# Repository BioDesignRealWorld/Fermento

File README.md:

Fermento
========

An open-source incubator for fun and profit. For more information about the project, see [biodesign.cc](http://biodesign.cc/2013/12/25/diy-incubator/).

Board
-----

* __Fab__ contains the PCB version to send to a professional PCB fabrication house. It has a nice silkscreen and slightly better component layout. 
* __Homebrew__ contains the version for homebrew PCB printing. The layout is one-sided for easier manufacturing. Drill plan and assembly instruction sheet included.
  To accomodate a single sided board, the wiring of the component to the microcontroller had to be changed. The correct pin mapping can be changed by a single line
  in the firmware.

Bill Of Material
----------------

* 1x ATmega328p
* 1x DIP28 socket 
* 2x Tactile switch (through hole) (BUTTON1, BUTTON2) (C&K PTS645SM95-2 LFS)
* 2x Resistor 10K (R1, R3)
* 1x Resistor 1K (R2)
* 4x Capacitor 0.1uF, 2.5 mm pin spacing (C1, C2, C3, C5)
* 1x Electrolytic capacitor 47uF, radial, 2.5 mm pin spacing (C4)
* 1x 6-pin 90-degrees header (SERIAL)
* 1x 3x2-pin straight header (ISP)
* 1x 6-terminal screw block (Altech MBE-156)
* 1x Relay, 3VDC switching (Omron G6RL-1A-DC3)
* 1x 13mm buzzer (BUZZ1) (Murata, PKM13EPYH4000-A0)
* 1x DC jack 2.1mm (Kobiconn 163-179PH-EX)
* 1x 32.768kHz crystal (Q1) (ECS-.327-12.5-13X)
* 1x Mosfet transistor, TO92 (Q2) (Supertex TP2104N3-G)
* 1x 3.3V Regulator, TO220 (REG1) (TI TLV2217-33KCSE3)
* 1x Temperature sensor, TO92 (TEMP1) (TI LM61CIZ/NOPB)
* 1x 7-segment 4-digit display (7SEG) (Lumex LDQ-N514RI)

Wiring of the incubator
-----------------------

The board has a 6 pin terminal that allows minimal effort in wiring all the AC part of the circuit.

* The 2 wires from the bulb socket go into __LOAD__.
* The 2 wires from the plug go into one of the __AC IN__ terminal.
* The second __AC IN__ can be used to attach a female AC socket. This allows to connect there a DC outlet to power the board.

Power supply
------------

The board has a 2.1mm DC jack. The DC regulator requires an input of 3-12V DC.

Firmware
--------

To install the firmware in your Arduino IDE, do the following.

* Copy the folder `firmware/Fermento` to your local Arduino folder.
* Copy the content of `firmware/hardware` to local `Arduino/hardware`.
* Copy the content of `firmware/libraries` to local `Arduino/libraries`.

Then, chose `Tools -> Board -> ATmega328p on a breadboard`. Choose the sketch
`Fermento` from the sketchbook, and upload it.

In case you don't use the homebrew version, there is one line to comment out in
the sketch to change the pin mapping.

In the Fab version, an ISP header is provided to burn the bootloader. The Homebrew
version is lacking this, so a different board (such as the standard Arduino) needs
to be used to burn the bootloader. In addition, an ISP-programmer is needed.
An Arduino board can also be used to do [the job](http://arduino.cc/en/Tutorial/ArduinoISP).

Use it
------

Button1 and button2 control the incubation temperature and time respectively.

When button1 is shortly pressed the display switches to temperature. To set the
incubation temperature, keep button1 pressed until it displays the desired
temperature. The temperature regulation starts as soon as an incubation
temperatures different than 0 is set. Note that if the incubation temperature
is lower than room temperature, nothing happens.

When button2 is shortly pressed the display switches to incubation time
(hours:minutes). To set the incubation time, keep button2 pressed until the
desired incubation time is displayed. If you don’t set an incubation time, the
incubation will never stop. The time goes up in increments of 30 minutes.

Pressing button1 and button2 together for a few seconds resets incubation temperature and time to 0.

License
-------

2013 (c) Robin Scheibler, [CC BY-SA 3.0](https://creativecommons.org/licenses/by-sa/3.0/).

Based on [TokyoTime](http://robinscheibler.org/TokyoTime), itself based on SparkFun's [BigTime](https://www.sparkfun.com/products/11734).

The code uses the [Arduino PID library](http://playground.arduino.cc/Code/PIDLibrary).

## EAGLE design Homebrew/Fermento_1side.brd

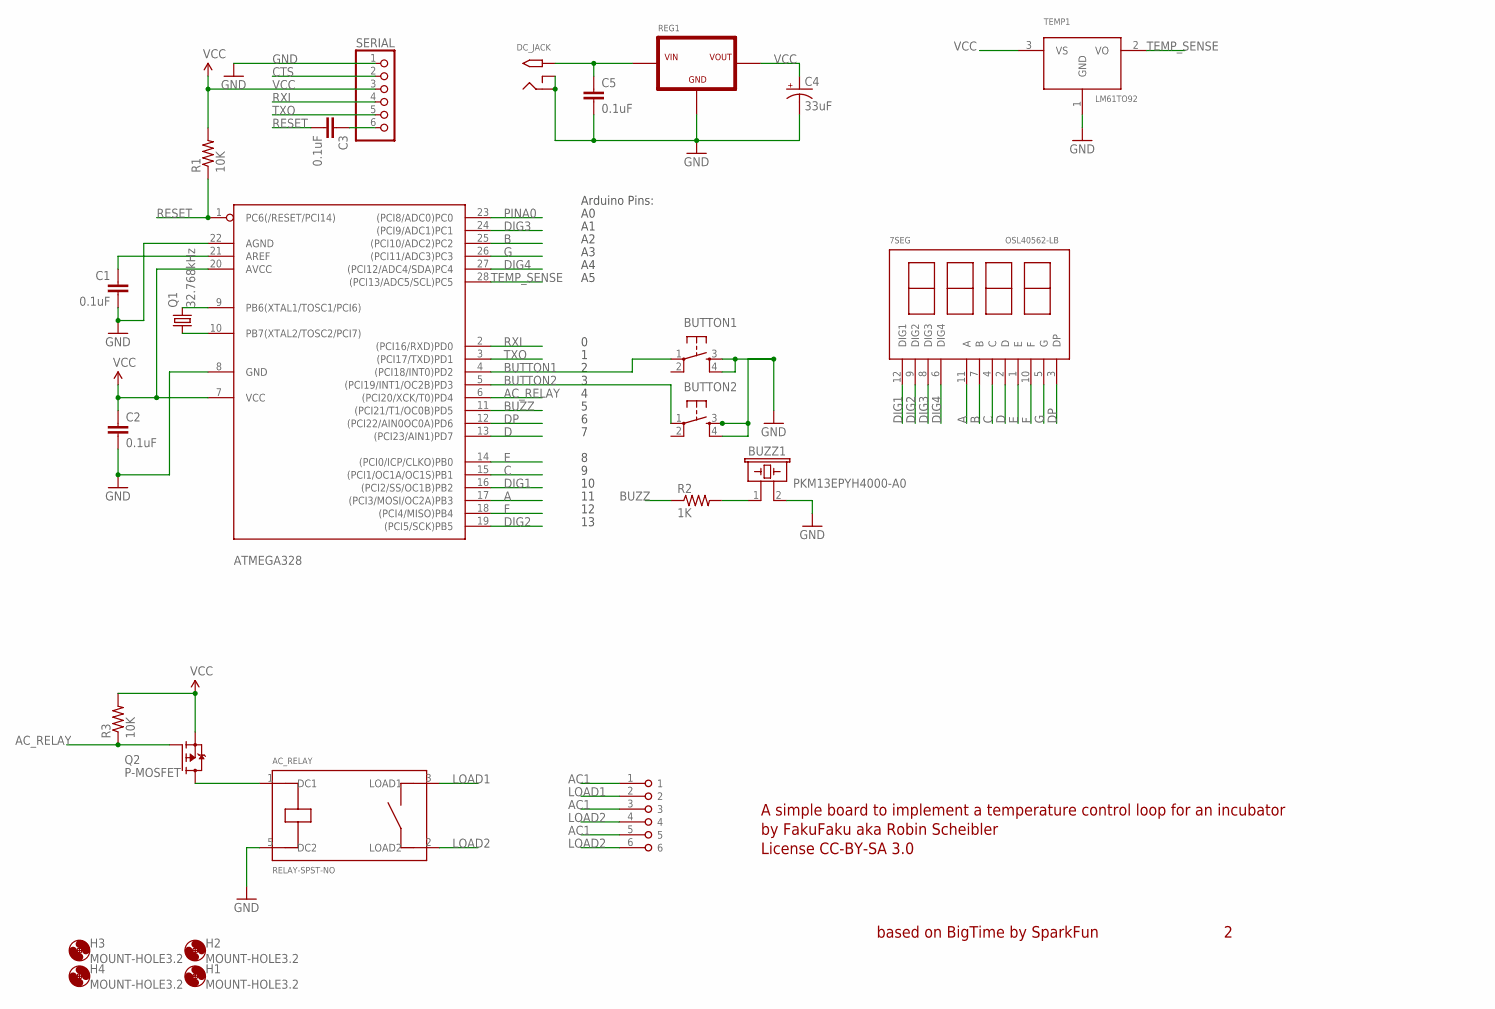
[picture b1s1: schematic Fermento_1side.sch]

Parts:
7SEG: OSL40562-LB; OSL40562
AC_RELAY: RELAY-SPST-NO; G6RL-1A-DC3
ATMEGA328: ATMEGA168-20P; DIL28-3
BUTTON1, BUTTON2: TAC_SWITCHPTH; TACTILE-PTH
BUZZ1: PKM13EPYH4000-A0; PIEZO-MURATA-13MM
C1, C2, C3, C5: 0.1uF; CAP-PTH-SMALL
C4: 33uF; CPOL-RADIAL-10UF-25V
DC_JACK: 2.1MMJACKTHM; PJ-102A
H1, H2, H3, H4: MOUNT-HOLE3.2; 3,2
Q1: 32.768kHz; CRYSTAL-8X3-TH
Q2: P-MOSFET; TO92-
R1, R3: 10K; 0207/10
R2: 1K; 0207/10
REG1: REGULATOR-NOTHERMAL-TO220-STRAIGHT; TO-220-STRAIGHT
SERIAL: PINHD-1X6/90; 1X06/90
TEMP1: LM61TO92; TO92-
U$2: TERMINAL-6; MBE-156

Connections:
A: 7SEG.11 (A), ATMEGA328.17 ((PCI3/MOSI/OC2A)PB3)
AC1: U$2.1, U$2.3, U$2.5
AC_RELAY: ATMEGA328.6 ((PCI20/XCK/T0)PD4), Q2.2 (G), R3.1
AREF: ATMEGA328.21 (AREF), C1.1
B: 7SEG.7 (B), ATMEGA328.25 ((PCI10/ADC2)PC2)
BUTTON1: ATMEGA328.4 ((PCI18/INT0)PD2), BUTTON1.1
BUTTON2: ATMEGA328.5 ((PCI19/INT1/OC2B)PD3), BUTTON2.1
BUZZ: ATMEGA328.11 ((PCI21/T1/OC0B)PD5), R2.1
C: 7SEG.4 (C), ATMEGA328.15 ((PCI1/OC1A/OC1S)PB1)
CTS: SERIAL.2
D: 7SEG.2 (D), ATMEGA328.13 ((PCI23/AIN1)PD7)
DIG1: 7SEG.12 (DIG1), ATMEGA328.16 ((PCI2/SS/OC1B)PB2)
DIG2: 7SEG.9 (DIG2), ATMEGA328.19 ((PCI5/SCK)PB5)
DIG3: 7SEG.8 (DIG3), ATMEGA328.24 ((PCI9/ADC1)PC1)
DIG4: 7SEG.6 (DIG4), ATMEGA328.27 ((PCI12/ADC4/SDA)PC4)
DP: 7SEG.3 (DP), ATMEGA328.12 ((PCI22/AIN0OC0A)PD6)
E: 7SEG.1 (E), ATMEGA328.14 ((PCI0/ICP/CLKO)PB0)
F: 7SEG.10 (F), ATMEGA328.18 ((PCI4/MISO)PB4)
G: 7SEG.5 (G), ATMEGA328.26 ((PCI11/ADC3)PC3)
GND: AC_RELAY.5 (DC2), ATMEGA328.8 (GND), ATMEGA328.22 (AGND), BUTTON1.3, BUTTON1.4, BUTTON2.3, BUTTON2.4, BUZZ1.2, C1.2, C2.2, C4.2 (-), C5.2, DC_JACK.RING, DC_JACK.RING_SW, REG1.CENTER (GND), SERIAL.1, TEMP1.1 (GND)
LOAD1: AC_RELAY.3 (LOAD1), U$2.2
LOAD2: AC_RELAY.2 (LOAD2), U$2.4, U$2.6
unnamed: ATMEGA328.9 (PB6(XTAL1/TOSC1/PCI6)), Q1.2
unnamed: ATMEGA328.10 (PB7(XTAL2/TOSC2/PCI7)), Q1.1
unnamed: C5.1, DC_JACK.TIP, REG1.LEFT (VIN)
unnamed: C3.1, SERIAL.6
unnamed: BUZZ1.1, R2.2
PINA0: ATMEGA328.23 ((PCI8/ADC0)PC0)
RELAY: AC_RELAY.1 (DC1), Q2.1 (D)
RESET: ATMEGA328.1 (PC6(/RESET/PCI14)), C3.2, R1.1
RXI: ATMEGA328.2 ((PCI16/RXD)PD0), SERIAL.4
TEMP_SENSE: ATMEGA328.28 ((PCI13/ADC5/SCL)PC5), TEMP1.2 (VO)
TXO: ATMEGA328.3 ((PCI17/TXD)PD1), SERIAL.5
VCC: ATMEGA328.7 (VCC), ATMEGA328.20 (AVCC), C2.1, C4.1 (+), Q2.3 (S), R1.2, R3.2, REG1.RIGHT (VOUT), SERIAL.3, TEMP1.3 (VS)

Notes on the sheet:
A simple board to implement a temperature control loop for an incubator
by FakuFaku aka Robin Scheibler
License CC-BY-SA 3.0
based on BigTime by SparkFun
Arduino Pins:

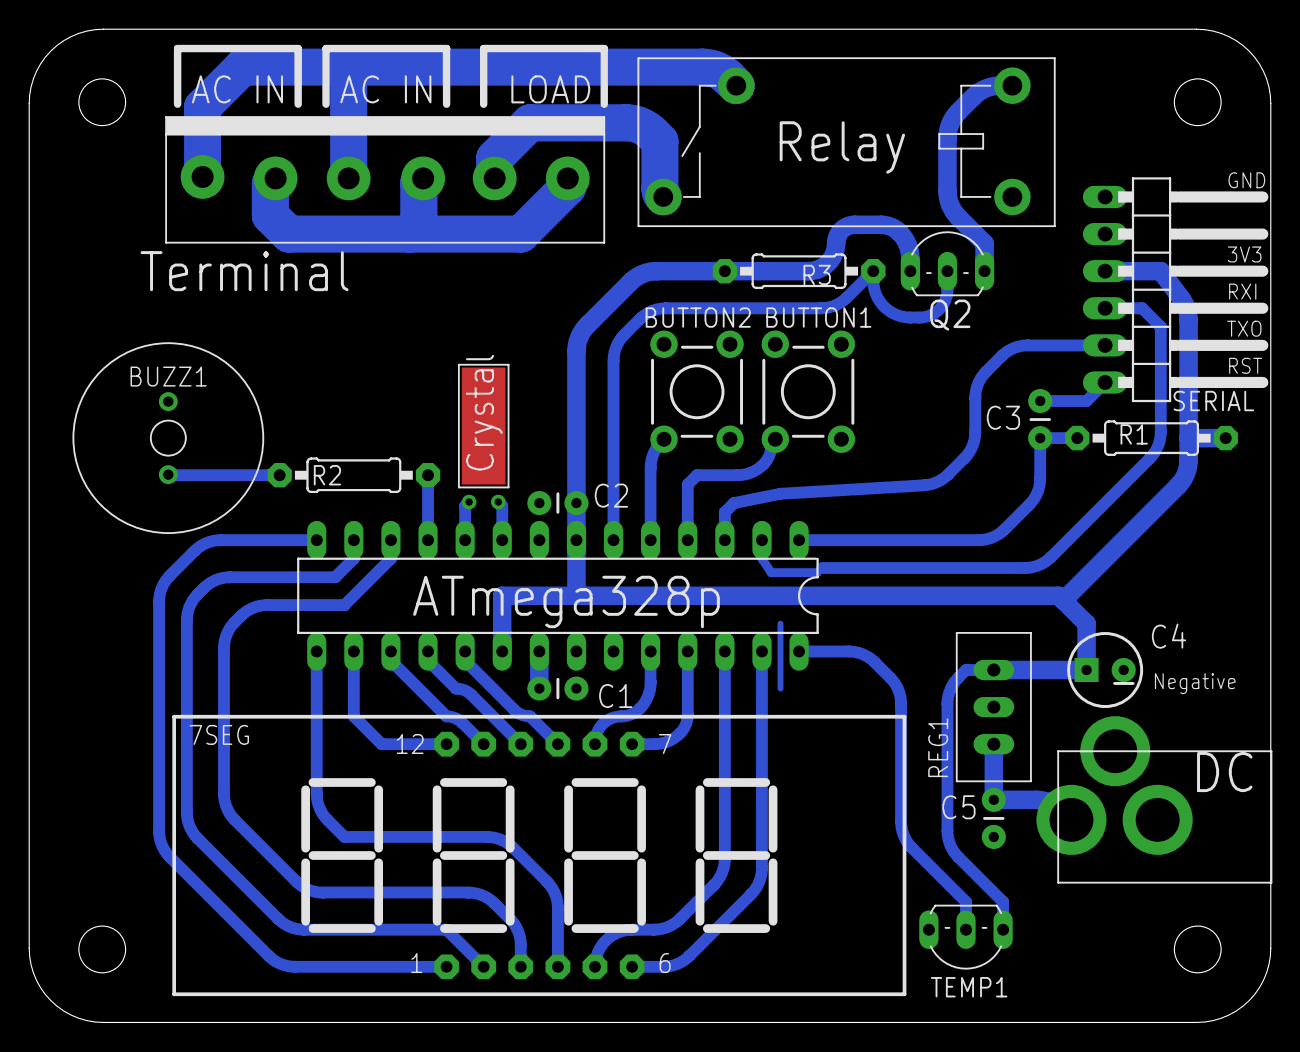
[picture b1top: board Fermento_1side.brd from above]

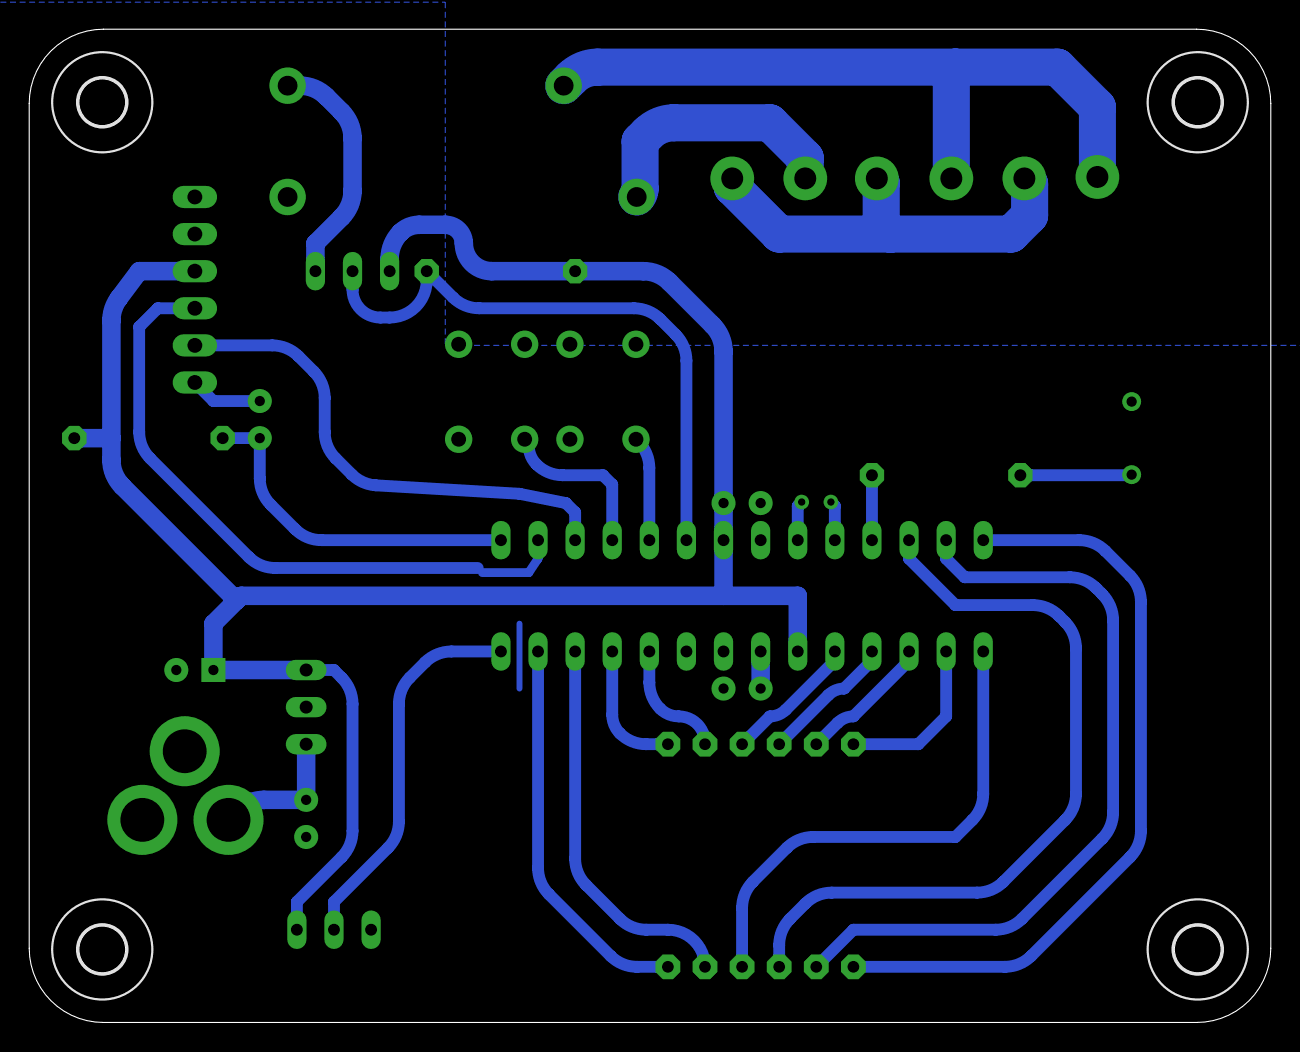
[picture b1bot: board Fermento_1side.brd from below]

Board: 2 copper layers, 85.0 x 68.0 mm, 25 parts (4 on the bottom side), 32 nets.

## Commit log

2013-11-19 Initial commit.
2013-11-19 Added the one-sided version.
2013-11-19 Added 1 sided version and png images.
2013-11-20 Added mask and info diagram for 1sided homebrew incubator.
2013-11-20 board difference added to README.
2013-11-20 One sided homebrew-friendly design redone.
2013-11-27 Added firmware to the repo.
2013-11-27 Added fermento arduino sketch.
2013-11-27 Updated license in Fermento sketch.
2013-11-28 README.
2013-11-29 BOM in README.
2013-12-04 Now incubator is on by default. Also there was a bug in reset function.
2013-12-25 Cleaned up for biodesign.cc post.
2013-12-25 Added license to readme.
2013-12-25 Bootloader footnote.
2014-01-10 Added the mask file for homebrew pcb.
2014-04-21 Fixed the time display bug. Fixed the seven sement digit_on/off segment_on/off bug.
2014-04-23 Fixed name of microcontroller in README and boards.txt file.
2014-04-23 Added kindof datasheet for Fab board.
2014-04-23 Added labels in the parts list.
2014-05-02 Remove a wrong pin pushed by mistake to the repo. Added an option to use LM35 sensor and an option for easily changing the ADC voltage repference.
2014-05-05 Corrected typo in hash def that prevented compilation.
2014-06-01 Added ATmega328p to bill of material (duh).
2019-12-01 add open know-how manifest file
2022-02-14 Various OKH fixes
    * YAML syntax fixes
    * use BCP 47 compliant language identifiers
    * use SPDX compliant license identifiers
